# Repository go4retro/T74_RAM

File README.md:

# TI74 Battery Backed RAM Cartridge

## Introduction

Reproduction of the Texas Instruments TI-74 Battery Backed RAM Cartridge.  The implementation is based on material from [TEXAS TI-74 BASICALC &amp; 8K RAM Cartridge teardown](https://www.hpmuseum.org/forum/thread-7146.html). The discussion on creating this cartridge is at [TI-74 RAM Cartridges - Tomy Tutor, CC40, 99/2, 99/8, Cortex, 990 mini - AtariAge Forums](https://forums.atariage.com/topic/364366-ti-74-ram-cartridges/)

## Requirements

- TI-74

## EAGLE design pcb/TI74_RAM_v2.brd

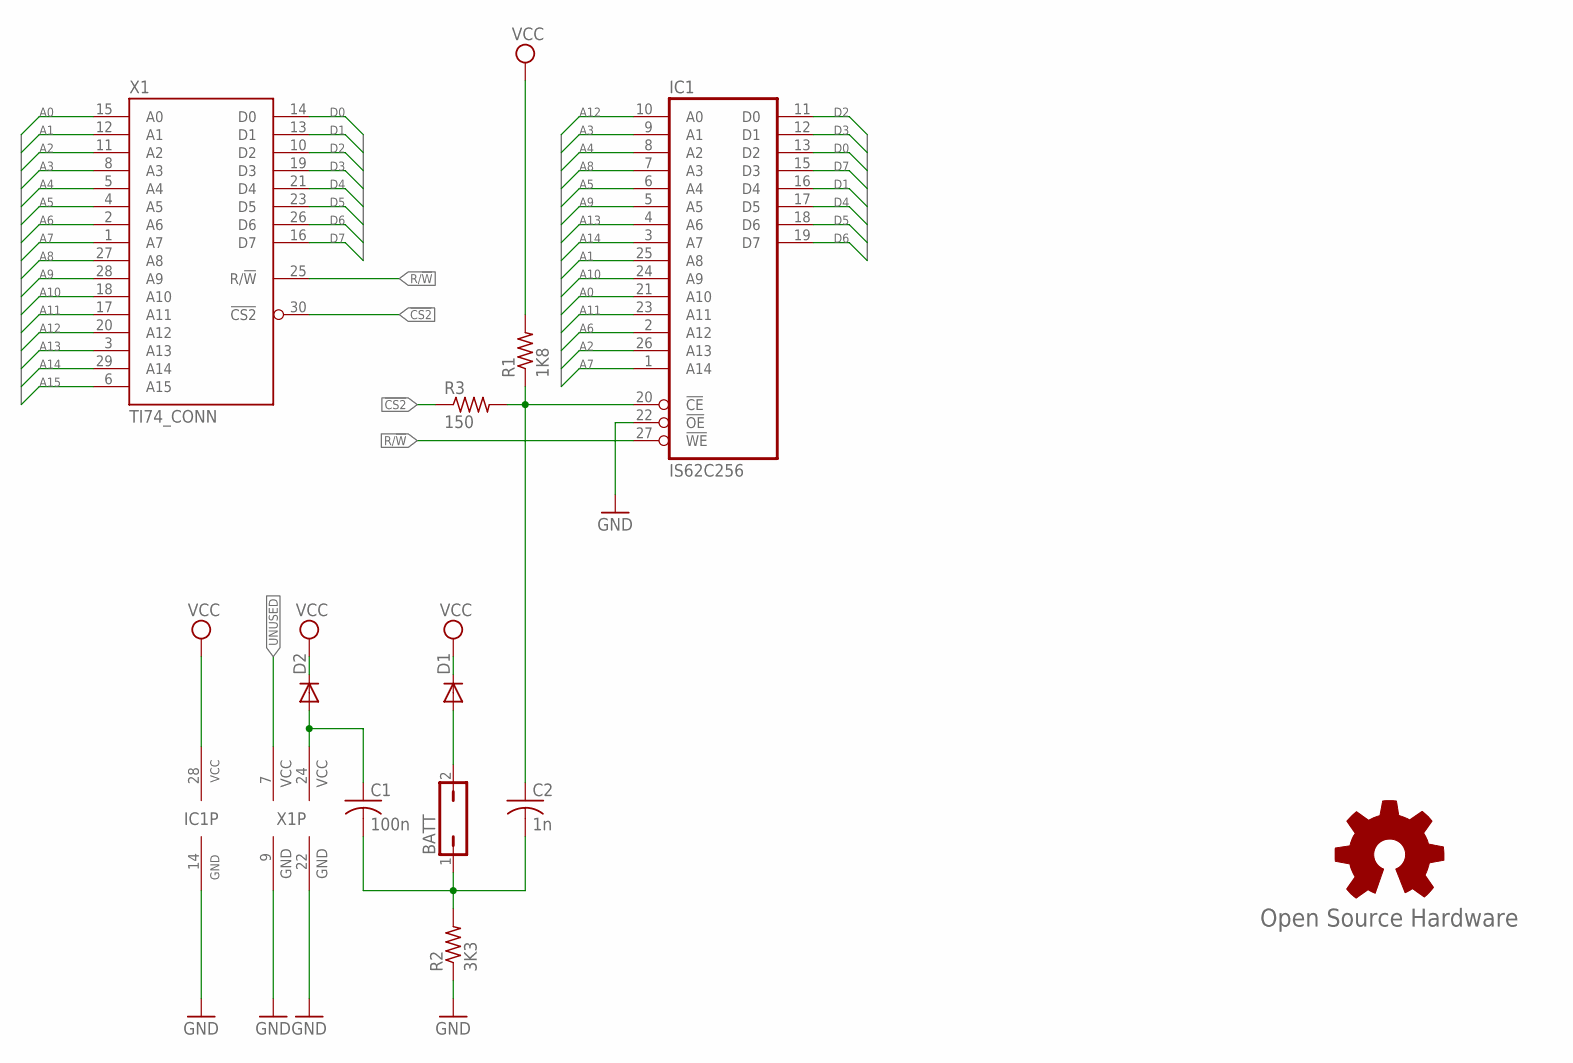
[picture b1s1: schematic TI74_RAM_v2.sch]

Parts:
BATT: JP1Q; JP1
C1: 100n; C0603
C2: 1n; C0603
D1, D2: DIODE-SOD323-W; SOD323-W
GOLD_ORB_SM1: Open Source Hardware; OSHW_5MM
IC1: IS62C256; SO28L
R1: 1K8; R0603
R2: 3K3; R0603
R3: 150; R0603
X1: TI74_CONN; MA050-15-2SHORT

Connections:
!CS2: R3.1, X1.30 (!CS2)
A0: IC1.21 (A10), X1.15 (A0)
A1: IC1.25 (A8), X1.12 (A1)
A2: IC1.26 (A13), X1.11 (A2)
A3: IC1.9 (A1), X1.8 (A3)
A4: IC1.8 (A2), X1.5 (A4)
A5: IC1.6 (A4), X1.4 (A5)
A6: IC1.2 (A12), X1.2 (A6)
A7: IC1.1 (A14), X1.1 (A7)
A8: IC1.7 (A3), X1.27 (A8)
A9: IC1.5 (A5), X1.28 (A9)
A10: IC1.24 (A9), X1.18 (A10)
A11: IC1.23 (A11), X1.17 (A11)
A12: IC1.10 (A0), X1.20 (A12)
A13: IC1.4 (A6), X1.3 (A13)
A14: IC1.3 (A7), X1.29 (A14)
A15: X1.6 (A15)
D0: IC1.13 (D2), X1.14 (D0)
D1: IC1.16 (D4), X1.13 (D1)
D2: IC1.11 (D0), X1.10 (D2)
D3: IC1.12 (D1), X1.19 (D3)
D4: IC1.17 (D5), X1.21 (D4)
D5: IC1.18 (D6), X1.23 (D5)
D6: IC1.19 (D7), X1.26 (D6)
D7: IC1.15 (D3), X1.16 (D7)
GND: IC1.14 (GND), IC1.22 (!OE), R2.1, X1.9 (GND), X1.22 (GND)
unnamed: C2.1, IC1.20 (!CE), R1.1, R3.2
unnamed: C1.1, D2.A, X1.24 (VCC_RAM)
unnamed: BATT.2, D1.A
unnamed: BATT.1, C1.2, C2.2, R2.2
R/!W: IC1.27 (!WE), X1.25 (R/!W)
UNUSED: X1.7 (VCC)
VCC: D1.C, D2.C, IC1.28 (VCC), R1.2

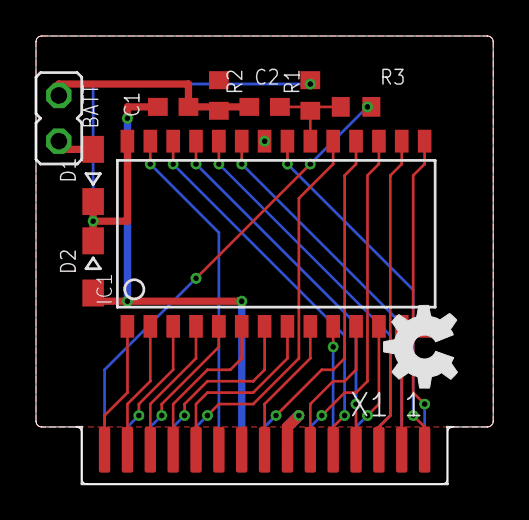
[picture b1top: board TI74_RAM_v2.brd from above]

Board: 2 copper layers, 25.4 x 24.9 mm, 11 parts (0 on the bottom side), 31 nets.

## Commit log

2024-04-30 Add README.md
2024-04-30 Update README.md again
2024-04-30 Update PCB Image
2024-05-01 Add in A14 address line
2024-06-01 Fixed A15->A0 mistake and shortened board (v2)
2024-06-05 small adjustments
